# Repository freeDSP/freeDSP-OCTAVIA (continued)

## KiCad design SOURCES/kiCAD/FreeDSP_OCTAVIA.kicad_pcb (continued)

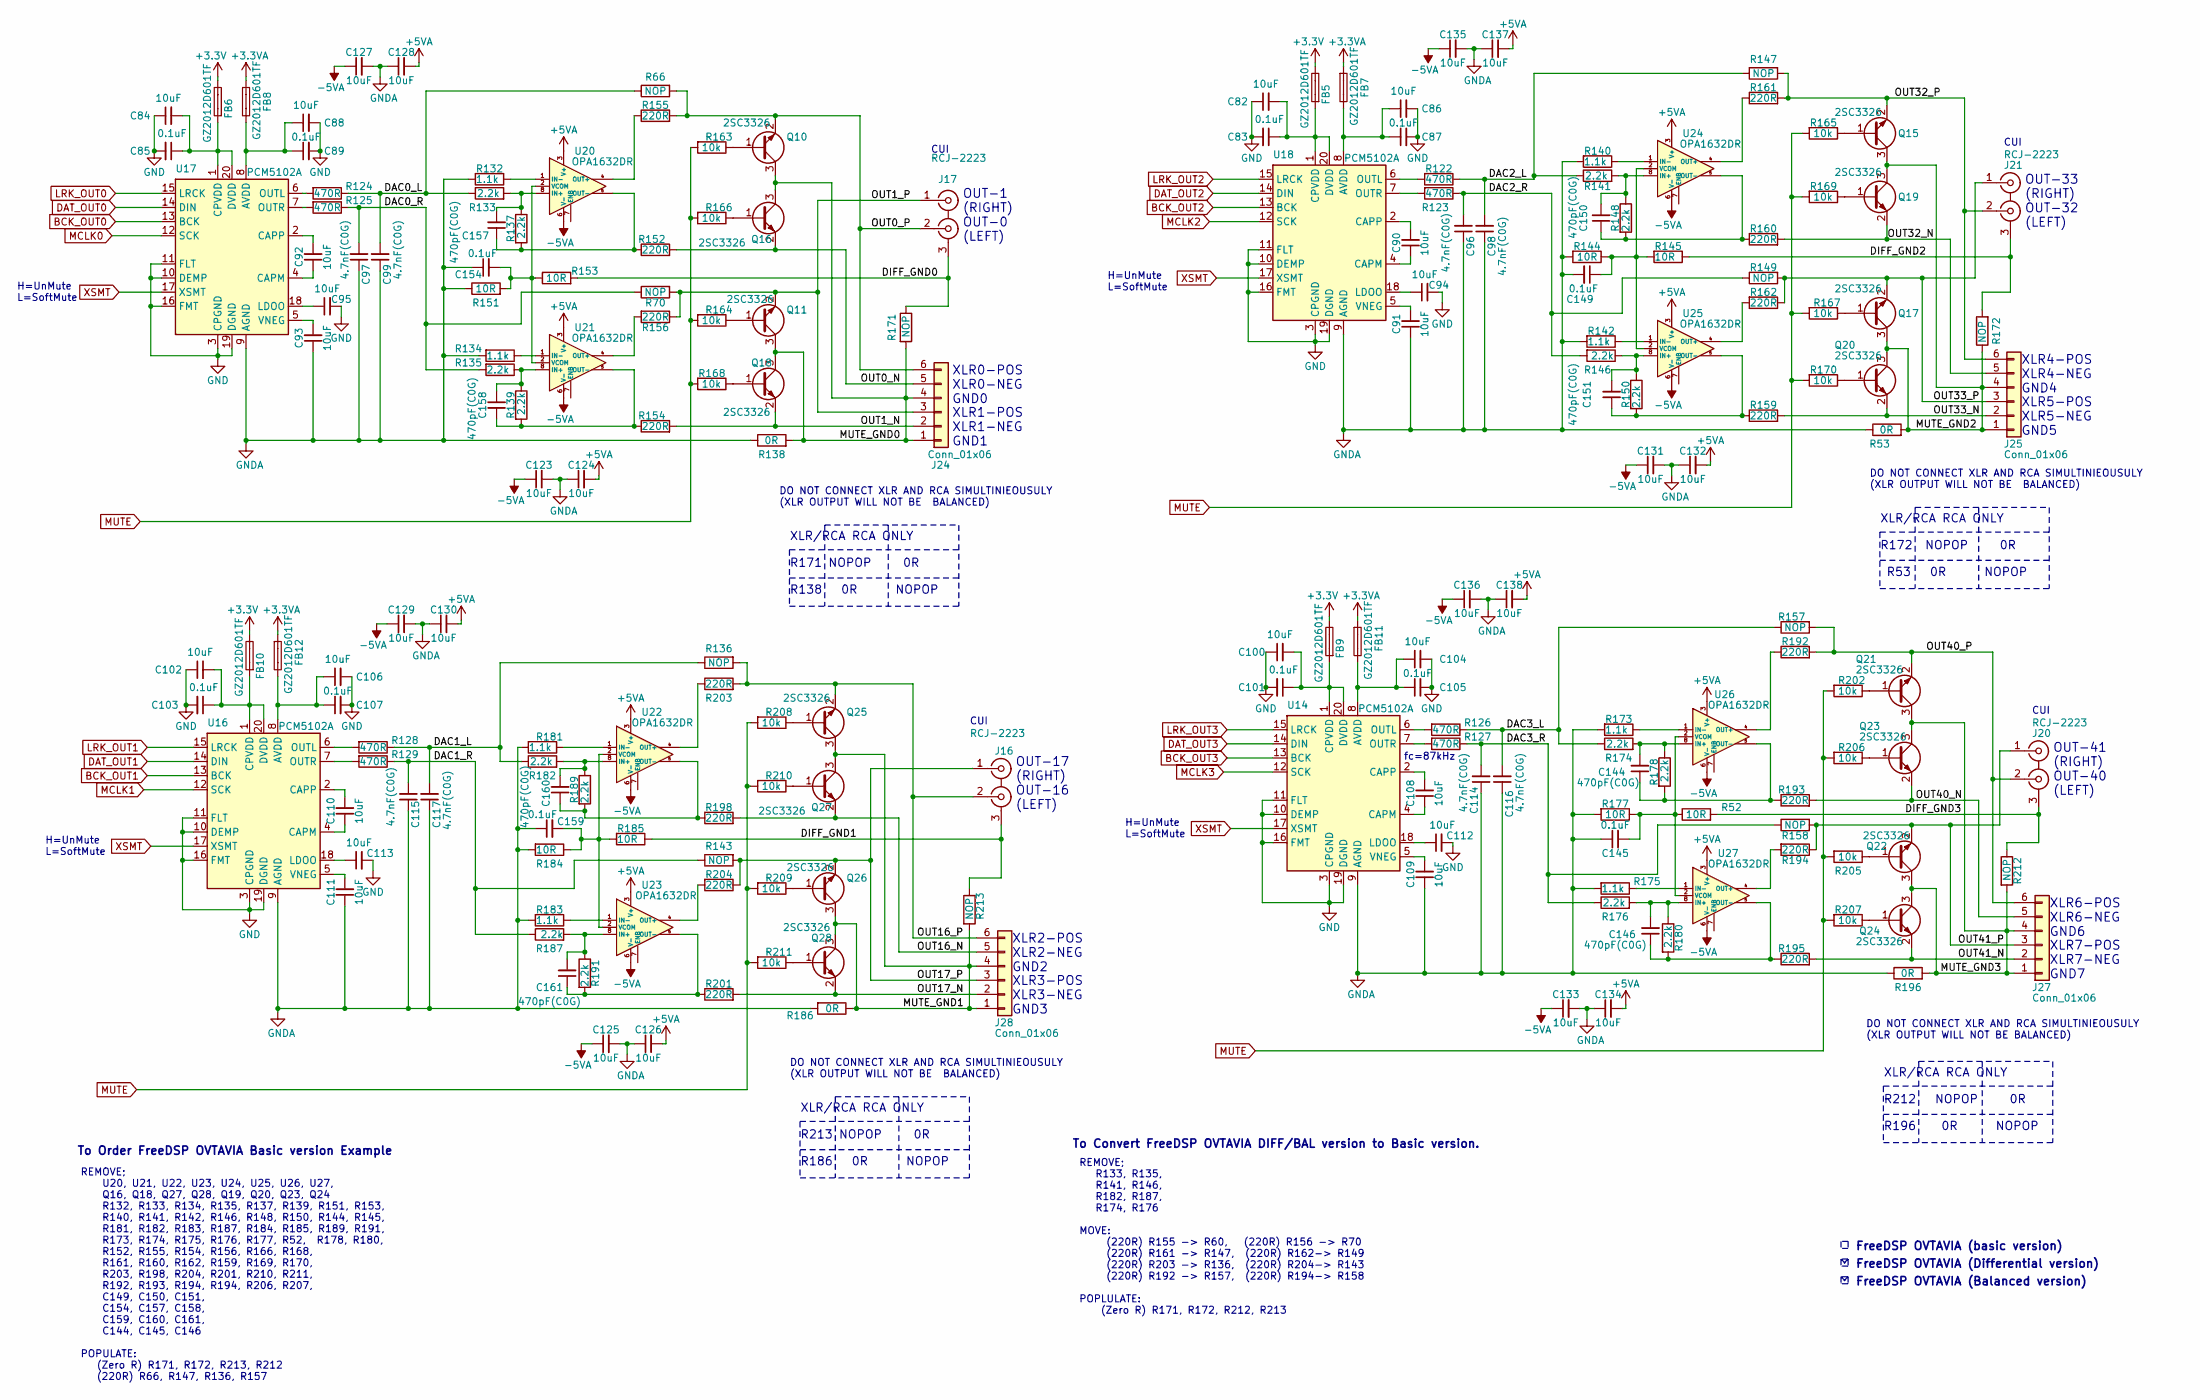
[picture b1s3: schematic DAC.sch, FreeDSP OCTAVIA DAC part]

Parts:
C82, C84, C86, C88, C102, C104, C106: 10uF; C_0805_2012Metric_Pad1.18x1.45mm_HandSolder
C83, C85, C87, C89, C103, C105, C107: 0.1uF; C_0805_2012Metric_Pad1.18x1.45mm_HandSolder
C90, C91, C92, C93, C94, C95, C108, C109, C110, C111, C112, C113, C123, C124, C125, C126, C127, C128, C129, C130, C131, C132, C133, C134, C135, C136, C137, C138: 10uF; C_0603_1608Metric
C96, C97, C98, C99, C114, C115, C116, C117: 4.7nF(C0G); C_0805_2012Metric_Pad1.18x1.45mm_HandSolder
C100: 10uF; C_0805_2012Metric
C101: 0.1uF; C_0805_2012Metric
C144, C146, C150, C151, C157, C158, C160, C161: 470pF(C0G); C_0805_2012Metric_Pad1.18x1.45mm_HandSolder
C145, C149, C154, C159: 0.1uF; C_0603_1608Metric
FB5, FB6, FB7, FB8, FB9, FB10, FB11, FB12: GZ2012D601TF; L_0805_2012Metric_Pad1.15x1.40mm_HandSolder
J16, J17, J20, J21: RCJ-2223
J24, J25, J27, J28: Conn_01x06; PinHeader_1x06_P2.54mm_Vertical
Q10, Q11, Q15, Q16, Q17, Q18, Q19, Q20, Q21, Q22, Q23, Q24, Q25, Q26, Q27, Q28: 2SC3326; SOT-23
R52, R144, R145, R151, R153, R177, R184, R185: 10R; R_0603_1608Metric
R53, R138, R186, R196: 0R; R_0603_1608Metric
R66, R70, R136, R143, R147, R149, R157, R158: NOP; R_0603_HandSoldering
R122, R123, R124, R125, R126, R127, R128, R129: 470R; R_0603_1608Metric
R132, R134, R140, R142, R173, R175, R181, R183: 1.1k; R_0603_1608Metric
R133, R135, R137, R139, R141, R146, R148, R150, R174, R176, R178, R180, R182, R187, R189, R191: 2.2k; R_0603_1608Metric
R152, R154, R155, R156, R159, R160, R161, R162, R192, R193, R194, R195, R198, R201, R203, R204: 220R; R_0603_1608Metric
R163, R164, R165, R166, R167, R168, R169, R170, R202, R205, R206, R207, R208, R209, R210, R211: 10k; R_0603_1608Metric
R171, R172, R212, R213: NOP; R_0603_1608Metric_Pad0.98x0.95mm_HandSolder
U14, U16, U17, U18: PCM5102A; TSSOP-20_4.4x6.5mm_P0.65mm
U20, U21, U22, U23, U24, U25, U26, U27: OPA1632DR; SOIC127P600X175-8N

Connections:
+3.3VA: FB7.1, FB8.1, FB11.1, FB12.1; also elsewhere on the board
+3V3: FB5.2, FB6.2, FB9.2, FB10.2; also elsewhere on the board
+5VA: C124.2, C126.2, C128.2, C130.2, C132.2, C134.2, C137.2, C138.2, U20.3 (V+), U21.3 (V+), U22.3 (V+), U23.3 (V+), U24.3 (V+), U25.3 (V+), U26.3 (V+), U27.3 (V+); also elsewhere on the board
-5VA: C123.1, C125.1, C127.1, C129.1, C131.1, C133.1, C135.1, C136.1, U20.6 (V-), U21.6 (V-), U22.6 (V-), U23.6 (V-), U24.6 (V-), U25.6 (V-), U26.6 (V-), U27.6 (V-); also elsewhere on the board
/ADC_IO Part/DAC/DAC0_L: C99.2, R66.1, R124.1, R133.1
/ADC_IO Part/DAC/DAC0_R: C97.2, R70.1, R125.1, R135.2
/ADC_IO Part/DAC/DAC1_L: C117.2, R128.1, R136.1, R182.1
/ADC_IO Part/DAC/DAC1_R: C115.2, R129.1, R143.1, R187.1
/ADC_IO Part/DAC/DAC2_L: C98.2, R122.1, R141.1, R147.1
/ADC_IO Part/DAC/DAC2_R: C96.2, R123.1, R146.2, R149.1
/ADC_IO Part/DAC/DAC3_L: C116.2, R126.1, R157.1, R174.1
/ADC_IO Part/DAC/DAC3_R: C114.2, R127.1, R158.1, R176.1
/ADC_IO Part/DAC/DIFF_GND0: J17.3 (EXT), R153.2, R171.1
/ADC_IO Part/DAC/DIFF_GND1: J16.3 (EXT), R185.1, R213.1
/ADC_IO Part/DAC/DIFF_GND2: J21.3 (EXT), R145.1, R172.2
/ADC_IO Part/DAC/DIFF_GND3: J20.3 (EXT), R52.2, R212.1
/ADC_IO Part/DAC/MUTE_GND0: J24.1, J24.4, Q10.3 (C), Q11.3 (C), Q16.3 (C), Q18.3 (C), R138.2, R171.2
/ADC_IO Part/DAC/MUTE_GND1: J28.1, J28.4, Q25.3 (C), Q26.3 (C), Q27.3 (C), Q28.3 (C), R186.1, R213.2
/ADC_IO Part/DAC/MUTE_GND2: J25.1, J25.4, Q15.3 (C), Q17.3 (C), Q19.3 (C), Q20.3 (C), R53.2, R172.1
/ADC_IO Part/DAC/MUTE_GND3: J27.1, J27.4, Q21.3 (C), Q22.3 (C), Q23.3 (C), Q24.3 (C), R196.2, R212.2
/ADC_IO Part/DAC/OUT0_N: J24.5, Q16.2 (E), R152.2
/ADC_IO Part/DAC/OUT0_P: J17.2 (IN2), J24.6, Q10.2 (E), R66.2, R155.2
/ADC_IO Part/DAC/OUT1_N: J24.2, Q18.2 (E), R154.2
/ADC_IO Part/DAC/OUT1_P: J17.1 (IN1), J24.3, Q11.2 (E), R70.2, R156.1
/ADC_IO Part/DAC/OUT16_N: J28.5, Q27.2 (E), R198.2
/ADC_IO Part/DAC/OUT16_P: J16.2 (IN2), J28.6, Q25.2 (E), R136.2, R203.2
/ADC_IO Part/DAC/OUT17_N: J28.2, Q28.2 (E), R201.2
/ADC_IO Part/DAC/OUT17_P: J16.1 (IN1), J28.3, Q26.2 (E), R143.2, R204.1
/ADC_IO Part/DAC/OUT32_N: J25.5, Q19.2 (E), R160.2
/ADC_IO Part/DAC/OUT32_P: J21.2 (IN2), J25.6, Q15.2 (E), R147.2, R161.2
/ADC_IO Part/DAC/OUT33_N: J25.2, Q20.2 (E), R159.2
/ADC_IO Part/DAC/OUT33_P: J21.1 (IN1), J25.3, Q17.2 (E), R149.2, R162.1
/ADC_IO Part/DAC/OUT40_N: J27.5, Q23.2 (E), R193.2
/ADC_IO Part/DAC/OUT40_P: J20.2 (IN2), J27.6, Q21.2 (E), R157.2, R192.2
/ADC_IO Part/DAC/OUT41_N: J27.2, Q24.2 (E), R195.2
/ADC_IO Part/DAC/OUT41_P: J20.1 (IN1), J27.3, Q22.2 (E), R158.2, R194.1
BCK_OUT0: U17.13 (BCK); also elsewhere on the board
BCK_OUT1: U16.13 (BCK); also elsewhere on the board
BCK_OUT2: U18.13 (BCK); also elsewhere on the board
BCK_OUT3: U14.13 (BCK); also elsewhere on the board
DAT_OUT0: U17.14 (DIN); also elsewhere on the board
DAT_OUT1: U16.14 (DIN); also elsewhere on the board
DAT_OUT2: U18.14 (DIN); also elsewhere on the board
DAT_OUT3: U14.14 (DIN); also elsewhere on the board
GND: C82.1, C83.2, C84.1, C85.2, C86.2, C87.2, C88.2, C89.2, C94.2, C95.2, C100.1, C101.2, C102.1, C103.2, C104.2, C105.2, C106.2, C107.2, C112.2, C113.2, U14.3 (CPGND), U14.10 (DEMP), U14.11 (FLT), U14.16 (FMT), U14.19 (DGND), U16.3 (CPGND), U16.10 (DEMP), U16.11 (FLT), U16.16 (FMT), U16.19 (DGND), U17.3 (CPGND), U17.10 (DEMP), U17.11 (FLT), U17.16 (FMT), U17.19 (DGND), U18.3 (CPGND), U18.10 (DEMP), U18.11 (FLT), U18.16 (FMT), U18.19 (DGND); also elsewhere on the board
GNDA: C91.1, C93.1, C96.1, C97.1, C98.1, C99.1, C109.1, C111.1, C114.1, C115.1, C116.1, C117.1, C123.2, C124.1, C125.2, C126.1, C127.2, C128.1, C129.2, C130.1, C131.2, C132.1, C133.2, C134.1, C135.2, C136.2, C137.1, C138.1, C145.1, C149.2, C154.1, C159.1, R53.1, R132.2, R134.2, R138.1, R140.2, R142.2, R144.2, R151.1, R173.2, R175.2, R177.2, R181.2, R183.2, R184.2, R186.2, R196.1, U14.9 (AGND), U16.9 (AGND), U17.9 (AGND), U18.9 (AGND); also elsewhere on the board
LRK_OUT0: U17.15 (LRCK); also elsewhere on the board
LRK_OUT1: U16.15 (LRCK); also elsewhere on the board
LRK_OUT2: U18.15 (LRCK); also elsewhere on the board
LRK_OUT3: U14.15 (LRCK); also elsewhere on the board
MCLK0: U17.12 (SCK); also elsewhere on the board
MCLK1: U16.12 (SCK); also elsewhere on the board
MCLK2: U18.12 (SCK); also elsewhere on the board
MCLK3: U14.12 (SCK); also elsewhere on the board
MUTE: R163.2, R164.2, R165.2, R166.2, R167.2, R168.2, R169.2, R170.2, R202.2, R205.2, R206.2, R207.2, R208.2, R209.2, R210.2, R211.2; also elsewhere on the board
unnamed: C82.2, C83.1, FB5.1, U18.1 (CPVDD), U18.20 (DVDD)
unnamed: C84.2, C85.1, FB6.1, U17.1 (CPVDD), U17.20 (DVDD)
unnamed: C86.1, C87.1, FB7.2, U18.8 (AVDD)
unnamed: C88.1, C89.1, FB8.2, U17.8 (AVDD)
unnamed: C90.1, U18.4 (CAPM)
unnamed: C90.2, U18.2 (CAPP)
unnamed: C91.2, U18.5 (VNEG)
unnamed: C92.1, U17.4 (CAPM)
unnamed: C92.2, U17.2 (CAPP)
unnamed: C93.2, U17.5 (VNEG)
unnamed: C94.1, U18.18 (LDOO)
unnamed: C95.1, U17.18 (LDOO)
unnamed: C100.2, C101.1, FB9.1, U14.1 (CPVDD), U14.20 (DVDD)
unnamed: C102.2, C103.1, FB10.1, U16.1 (CPVDD), U16.20 (DVDD)
unnamed: C104.1, C105.1, FB11.2, U14.8 (AVDD)
unnamed: C106.1, C107.1, FB12.2, U16.8 (AVDD)
unnamed: C108.1, U14.4 (CAPM)
unnamed: C108.2, U14.2 (CAPP)
unnamed: C109.2, U14.5 (VNEG)
unnamed: C110.1, U16.4 (CAPM)
unnamed: C110.2, U16.2 (CAPP)
unnamed: C111.2, U16.5 (VNEG)
unnamed: C112.1, U14.18 (LDOO)
unnamed: C113.1, U16.18 (LDOO)
unnamed: C144.1, R178.2, R193.1, U26.5 (OUT-)
unnamed: C144.2, R174.2, R178.1, U26.8 (IN+)
unnamed: C145.2, R52.1, R177.1, U26.2 (VCOM), U27.2 (VCOM)
unnamed: C146.1, R180.2, R195.1, U27.5 (OUT-)
unnamed: C146.2, R176.2, R180.1, U27.8 (IN+)
unnamed: C149.1, R144.1, R145.2, U24.2 (VCOM), U25.2 (VCOM)
unnamed: C150.1, R148.2, R160.1, U24.5 (OUT-)
unnamed: C150.2, R141.2, R148.1, U24.8 (IN+)
unnamed: C151.1, R150.2, R159.1, U25.5 (OUT-)
unnamed: C151.2, R146.1, R150.1, U25.8 (IN+)
unnamed: C154.2, R151.2, R153.1, U20.2 (VCOM), U21.2 (VCOM)
unnamed: C157.1, R137.2, R152.1, U20.5 (OUT-)
unnamed: C157.2, R133.2, R137.1, U20.8 (IN+)
unnamed: C158.1, R139.2, R154.1, U21.5 (OUT-)
unnamed: C158.2, R135.1, R139.1, U21.8 (IN+)
unnamed: C159.2, R184.1, R185.2, U22.2 (VCOM), U23.2 (VCOM)
unnamed: C160.1, R189.2, R198.1, U22.5 (OUT-)
unnamed: C160.2, R182.2, R189.1, U22.8 (IN+)
unnamed: C161.1, R191.2, R201.1, U23.5 (OUT-)
unnamed: C161.2, R187.2, R191.1, U23.8 (IN+)
unnamed: Q10.1 (B), R163.1
unnamed: Q11.1 (B), R164.1
unnamed: Q15.1 (B), R165.1
unnamed: Q16.1 (B), R166.1
unnamed: Q17.1 (B), R167.1
unnamed: Q18.1 (B), R168.1
unnamed: Q19.1 (B), R169.1
unnamed: Q20.1 (B), R170.1
unnamed: Q21.1 (B), R202.1
unnamed: Q22.1 (B), R205.1
unnamed: Q23.1 (B), R206.1
unnamed: Q24.1 (B), R207.1
unnamed: Q25.1 (B), R208.1
unnamed: Q26.1 (B), R209.1
unnamed: Q27.1 (B), R210.1
unnamed: Q28.1 (B), R211.1
unnamed: R122.2, U18.6 (OUTL)
unnamed: R123.2, U18.7 (OUTR)
unnamed: R124.2, U17.6 (OUTL)
unnamed: R125.2, U17.7 (OUTR)
unnamed: R126.2, U14.6 (OUTL)
unnamed: R127.2, U14.7 (OUTR)
unnamed: R128.2, U16.6 (OUTL)
unnamed: R129.2, U16.7 (OUTR)
unnamed: R132.1, U20.1 (IN-)
unnamed: R134.1, U21.1 (IN-)
unnamed: R140.1, U24.1 (IN-)
unnamed: R142.1, U25.1 (IN-)
unnamed: R155.1, U20.4 (OUT+)
unnamed: R156.2, U21.4 (OUT+)
unnamed: R161.1, U24.4 (OUT+)
unnamed: R162.2, U25.4 (OUT+)
unnamed: R173.1, U26.1 (IN-)
unnamed: R175.1, U27.1 (IN-)
unnamed: R181.1, U22.1 (IN-)
unnamed: R183.1, U23.1 (IN-)
unnamed: R192.1, U26.4 (OUT+)
unnamed: R194.2, U27.4 (OUT+)
unnamed: R203.1, U22.4 (OUT+)
unnamed: R204.2, U23.4 (OUT+)
XSMT: U14.17 (XSMT), U16.17 (XSMT), U17.17 (XSMT), U18.17 (XSMT); also elsewhere on the board

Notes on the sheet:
FreeDSP OVTAVIA (basic version)
FreeDSP OVTAVIA (Differential version)
XLR6-POS XLR6-NEG GND6
XLR2-POS XLR2-NEG GND2
XLR5-POS XLR5-NEG GND5
XLR7-POS XLR7-NEG GND7
XLR3-POS XLR3-NEG GND3
XLR1-POS XLR1-NEG GND1
XLR4-POS XLR4-NEG GND4
XLR0-POS XLR0-NEG GND0
OUT-33 (RIGHT) OUT-32 (LEFT)
OUT-41 (RIGHT) OUT-40 (LEFT)
OUT-17 (RIGHT) OUT-16 (LEFT)
To Order FreeDSP OVTAVIA Basic version Example
XLR/RCA RCA ONLY R212 NOPOP 0R R196 0R NOPOP
REMOVE; U20, U21, U22, U23, U24, U25, U26, U27, Q16, Q18, Q27, Q28, Q19, Q20, Q23, Q24 R132, R133, R134, R135, R137, R139, R151, R153, R140, R141, R142, R146, R148, R150, R144, R145, R181, R182, R183, R187, R184, R185, R189, R191, R173, R174, R175, R176, R177, R52, R178, R180, R152, R155, R154, R15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
H=UnMute L=SoftMute
FreeDSP OVTAVIA (Balanced version)
DO NOT CONNECT XLR AND RCA SIMULTINIEOUSULY (XLR OUTPUT WILL NOT BE BALANCED)
DO NOT CONNECT XLR AND RCA SIMULTINIEOUSULY (XLR OUTPUT WILL NOT BE BALANCED)
OUT-1 (RIGHT) OUT-0 (LEFT)
XLR/RCA RCA ONLY R171 NOPOP 0R R138 0R NOPOP
XLR/RCA RCA ONLY R213 NOPOP 0R R186 0R NOPOP
XLR/RCA RCA ONLY R172 NOPOP 0R R53 0R NOPOP
fc=87kHz
CUI
To Convert FreeDSP OVTAVIA DIFF/BAL version to Basic version.
REMOVE; R133, R135, R141, R146, R182, R187, R174, R176 MOVE: (220R) R155 -> R60, (220R) R156 -> R70 (220R) R161 -> R147, (220R) R162-> R149 (220R) R203 -> R136, (220R) R204-> R143 (220R) R192 -> R157, (220R) R194-> R158 POPLULATE: (Zero R) R171, R172, R212, R213

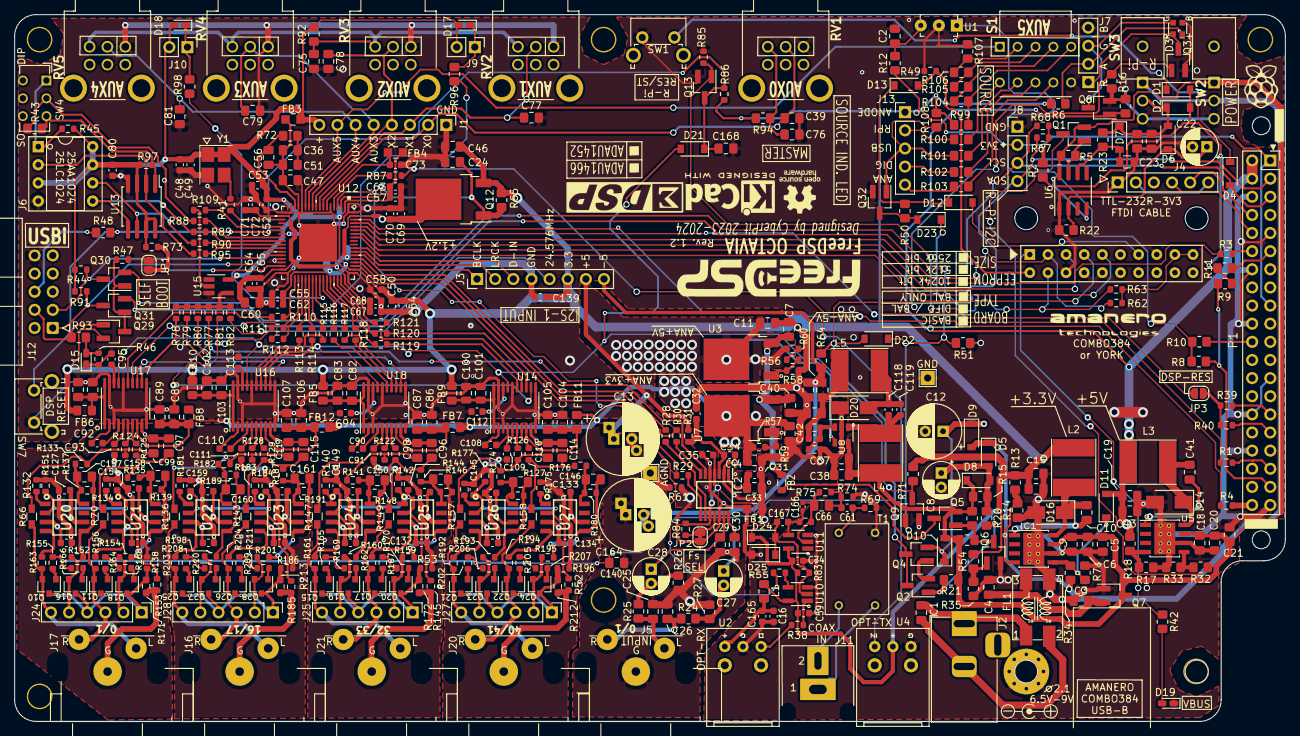
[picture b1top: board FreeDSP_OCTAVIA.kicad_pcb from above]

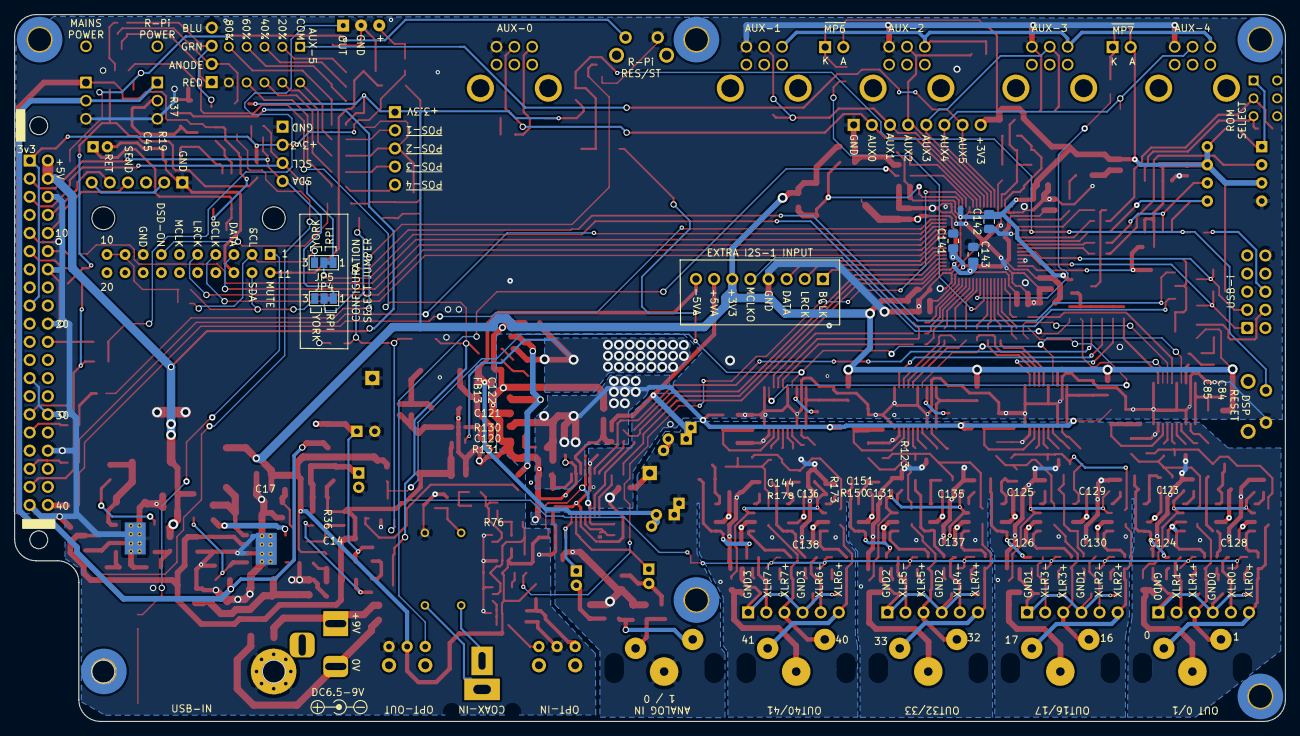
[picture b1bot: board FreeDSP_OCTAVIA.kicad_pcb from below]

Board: 4 copper layers, 178.0 x 99.0 mm, 525 parts (15 on the bottom side), 314 nets.

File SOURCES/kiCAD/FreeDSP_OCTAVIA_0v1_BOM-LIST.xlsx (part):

FreeDSP OCTAVIA Differential/Balanced Output Version BOM List
Date: | Wednesday, 15 March 2023 at 00:45:07
Component Count: | 487
Item | JLPCB# | Qty | Reference(s) | Value | Footprint | Description | Digi-Key_PN | Shop URL
 | HAND |  | A1 | Combo384 | MyLibrary:Combo384 | Amanero Combo384 or Compatible Module 20P Socket
 | OPTION |  | J6 | 8P_DIP_SOCKET | Package_DIP:DIP-8_W7.62mm_Socket | Only Mount if you need to use DIP package EEPROM
 | NOP |  | C66 | NOP | Capacitor_SMD:C_0805_2012Metric_Pad1.18x1.45mm_HandSolder
 | NOP |  | R9 | NOP | Resistor_SMD:R_0805_2012Metric_Pad1.20x1.40mm_HandSolder
 | NOP |  | R10 | NOP | Resistor_SMD:R_0805_2012Metric_Pad1.20x1.40mm_HandSolder
 | NOP |  | R40 | NOP | Resistor_SMD:R_0603_1608Metric
 | NOP |  | R143 | NOP | Resistor_SMD:R_0603_1608Metric
 | NOP |  | R144 | NOP | Resistor_SMD:R_0603_1608Metric
 | NOP |  | R145 | NOP | Resistor_SMD:R_0603_1608Metric
 | NOP |  | R184 | NOP | Resistor_SMD:R_0603_1608Metric
 | NOP |  | R185 | NOP | Resistor_SMD:R_0603_1608Metric
 | NOP |  | R186 | NOP | Resistor_SMD:R_0603_1608Metric
 | HAND |  | J1 | Conn_01x08 | Connector_PinHeader_2.54mm:PinHeader_1x08_P2.54mm_Vertical
 | HAND |  | J3 | Conn_01x08 | Connector_PinHeader_2.54mm:PinHeader_1x08_P2.54mm_Vertical
 | HAND |  | J4 | Header_01x06 | Connector_PinHeader_2.54mm:PinHeader_1x06_P2.54mm_Vertical
 | HAND |  | J5 | Conn_Coaxial_x2 | MyCompo:MJ-519 |  |  | https://akizukidenshi.com/catalog/g/gC-12480/
 | HAND |  | J8 | Header_01x04 | Connector_PinHeader_2.54mm:PinHeader_1x04_P2.54mm_Vertical
 | HAND |  | J11 | Conn_Coaxial | MyJacks:RJ-2410N | Yellow for SPDIF Coax. |  | https://akizukidenshi.com/catalog/g/gC-06508/
 | HAND |  | J12 | IDC_2x5 | Connector_IDC:IDC-Header_2x05_P2.54mm_Horizontal | or Angle type, for USBi
 | HAND |  | J13 | Conn_01x05 | Connector_PinHeader_2.54mm:PinHeader_1x05_P2.54mm_Vertical
 | HAND |  | J16 | MJ-519 | MyJacks:MJ-519 |  |  | https://akizukidenshi.com/catalog/g/gC-12480/
 | HAND |  | J17 | MJ-519 | MyJacks:MJ-519 |  |  | https://akizukidenshi.com/catalog/g/gC-12480/
 | HAND |  | J20 | MJ-519 | MyJacks:MJ-519 |  |  | https://akizukidenshi.com/catalog/g/gC-12480/
 | HAND |  | J21 | MJ-519 | MyJacks:MJ-519 |  |  | https://akizukidenshi.com/catalog/g/gC-12480/
 | HAND |  | J24 | Header6P | Connector_PinHeader_2.54mm:PinHeader_1x06_P2.54mm_Vertical
 | HAND |  | J25 | Conn_01x06 | Connector_PinHeader_2.54mm:PinHeader_1x06_P2.54mm_Vertical
 | HAND |  | J27 | Conn_01x06 | Connector_PinHeader_2.54mm:PinHeader_1x06_P2.54mm_Vertical
 | HAND |  | J28 | Header6P | Connector_PinHeader_2.54mm:PinHeader_1x06_P2.54mm_Vertical
 | HAND |  | P1 | Conn_02x20_Odd_Even | Connector_PinSocket_2.54mm:PinSocket_2x20_P2.54mm_Vertical
 | HAND |  | SW4 | SW_NOP_DPDT | Buttons_Switches_ThroughHole:SW_CuK_JS202011AQN_DPDT_Angled
 | HAND |  | C8 | 22uF/16V | Capacitor_THT:CP_Radial_D5.0mm_P2.00mm
 | HAND |  | C12 | 220uF/16V | Capacitor_THT:CP_Radial_D7.5mm_P2.50mm
 | HAND |  | C13 | 220uF/6.3V | Capacitor_THT:CP_Radial_D5.0mm_P2.00mm
 | HAND |  | C22 | 33uF/16V | Capacitor_THT:CP_Radial_D5.0mm_P2.00mm
 | HAND |  | C27 | 2.2uF | Capacitor_THT:CP_Radial_D5.0mm_P2.00mm
 | HAND |  | C28 | 2.2uF | Capacitor_THT:CP_Radial_D5.0mm_P2.00mm
 | HAND |  | J2 | DC12V-IN | Connector_BarrelJack:BarrelJack_Horizontal
 | HAND |  | RV1 | B10K | Myfootprints:RK09L12B0A31
 | HAND |  | RV2 | B10K | Myfootprints:RK09L12B0A31
 | HAND |  | RV3 | B10K | Myfootprints:RK09L12B0A31
 | HAND |  | RV4 | B10K | Myfootprints:RK09L12B0A31
 | HAND |  | RV5 | B10K | Myfootprints:RK09L12B0A31
 | HAND |  | S1 | SR10010F-0204-20F0B-C7-N-0027_ALT | Myfootprints:SR10010F020420F0BC7N0027 | Rotary Switches 2 POLE 4 POS D SHAFT |  | https://akizukidenshi.com/catalog/g/gP-16034/
 | HAND |  | SW1 | SW_Push | OPL_Switch:SW2-5.0-6.0X3.0X4.3MM
 | HAND |  | SW2 | SW_SPDT | Myfootprints:2MS1T1B4M7QES
 | HAND |  | SW3 | SW_SPDT | Myfootprints:2MS1T1B4M7QES
 | HAND |  | SW7 | DSP_RES | OPL_Switch:SW2-5.0-6.0X3.0X4.3MM | SWITCH PUSHBUTTON SPST 1A 30V | CW181-ND
 | HAND |  | T1 | PE-65612NL | PE65612NL | Audio Transformers / Signal Transformers THT Digital Audio 2500uH 1-Port
 | HAND |  | U1 | GP1UXC41QS | digikey-footprints:IR_Receiver_TSOP38238 | SENSOR REMOTE REC 38.0KHZ 45M | 751-1227-ND
 | HAND |  | U2 | PLR135-T10 | MyLibrary:PLR135-T10
 | HAND |  | U4 | PLT133-T10W | MyLibrary:PLT133-T10W
 | C9864 |  | IC1 | TPS5430DDA | Package_SO:TI_SO-PowerPAD-8_ThermalVias
 | C9864 |  | U5 | TPS5430DDA | Package_SO:TI_SO-PowerPAD-8_ThermalVias
 | C965848 |  | D3 | LED_ABGR | MyLED:LED_0603_ABGR
 | C96446 |  | C34 | 10uF | Capacitor_SMD:C_0603_1608Metric
 | C96446 |  | C50 | 10uF | Capacitor_SMD:C_0603_1608Metric
 | C96446 |  | C90 | 10uF | Capacitor_SMD:C_0603_1608Metric
 | C96446 |  | C91 | 10uF | Capacitor_SMD:C_0603_1608Metric
 | C96446 |  | C92 | 10uF | Capacitor_SMD:C_0603_1608Metric
 | C96446 |  | C93 | 10uF | Capacitor_SMD:C_0603_1608Metric
 | C96446 |  | C94 | 10uF | Capacitor_SMD:C_0603_1608Metric
 | C96446 |  | C95 | 10uF | Capacitor_SMD:C_0603_1608Metric
 | C96446 |  | C108 | 10uF | Capacitor_SMD:C_0603_1608Metric
 | C96446 |  | C109 | 10uF | Capacitor_SMD:C_0603_1608Metric
 | C96446 |  | C110 | 10uF | Capacitor_SMD:C_0603_1608Metric
 | C96446 |  | C111 | 10uF | Capacitor_SMD:C_0603_1608Metric
 | C96446 |  | C112 | 10uF | Capacitor_SMD:C_0603_1608Metric
 | C96446 |  | C113 | 10uF | Capacitor_SMD:C_0603_1608Metric
 | C96446 |  | C123 | 10uF | Capacitor_SMD:C_0603_1608Metric
 | C96446 |  | C124 | 10uF | Capacitor_SMD:C_0603_1608Metric
 | C96446 |  | C125 | 10uF | Capacitor_SMD:C_0603_1608Metric
 | C96446 |  | C126 | 10uF | Capacitor_SMD:C_0603_1608Metric
 | C96446 |  | C127 | 10uF | Capacitor_SMD:C_0603_1608Metric
 | C96446 |  | C128 | 10uF | Capacitor_SMD:C_0603_1608Metric
 | C96446 |  | C129 | 10uF | Capacitor_SMD:C_0603_1608Metric
 | C96446 |  | C130 | 10uF | Capacitor_SMD:C_0603_1608Metric
 | C96446 |  | C131 | 10uF | Capacitor_SMD:C_0603_1608Metric
 | C96446 |  | C132 | 10uF | Capacitor_SMD:C_0603_1608Metric
 | C96446 |  | C133 | 10uF | Capacitor_SMD:C_0603_1608Metric
 | C96446 |  | C134 | 10uF | Capacitor_SMD:C_0603_1608Metric
 | C96446 |  | C135 | 10uF | Capacitor_SMD:C_0603_1608Metric
 | C96446 |  | C136 | 10uF | Capacitor_SMD:C_0603_1608Metric
 | C96446 |  | C137 | 10uF | Capacitor_SMD:C_0603_1608Metric
 | C96446 |  | C138 | 10uF | Capacitor_SMD:C_0603_1608Metric
 | C908578 |  | FL1 | ACM9070 | MyLibrary:ACM9070 | TDK - ACM9070-701-2PL-TL01 - FILTER, COMMON MODE, 5A, SMD
 | C90760 |  | U6 | LMC555CMX | Package_SO:SOIC-8_3.9x4.9mm_P1.27mm
 | C86715 |  | U20 | OPA1632DR | Myfootprints:SOIC127P600X175-8N
 | C86715 |  | U21 | OPA1632DR | Myfootprints:SOIC127P600X175-8N
 | C86715 |  | U22 | OPA1632DR | Myfootprints:SOIC127P600X175-8N
 | C86715 |  | U23 | OPA1632DR | Myfootprints:SOIC127P600X175-8N
 | C86715 |  | U24 | OPA1632DR | Myfootprints:SOIC127P600X175-8N
 | C86715 |  | U25 | OPA1632DR | Myfootprints:SOIC127P600X175-8N
 | C86715 |  | U26 | OPA1632DR | Myfootprints:SOIC127P600X175-8N
 | C86715 |  | U27 | OPA1632DR | Myfootprints:SOIC127P600X175-8N
 | C8598 |  | D9 | SS2040FL | Diode_SMD:D_SOD-123
 | C8598 |  | D10 | SS2040FL | Diode_SMD:D_SOD-123
 | C8545 |  | Q3 | 2N7002 | Package_TO_SOT_SMD:SOT-23_Handsoldering
 | C8545 |  | Q6 | 2N7002 | Package_TO_SOT_SMD:SOT-23_Handsoldering
 | C8545 |  | Q8 | 2N7002 | Package_TO_SOT_SMD:SOT-23_Handsoldering
 | C8545 |  | Q9 | 2N7002 | Package_TO_SOT_SMD:SOT-23_Handsoldering
 | C8545 |  | Q13 | 2N7002 | Package_TO_SOT_SMD:SOT-23_Handsoldering
 | C8545 |  | Q14 | 2N7002 | Package_TO_SOT_SMD:SOT-23_Handsoldering
 | C8545 |  | Q30 | 2N7002 | Package_TO_SOT_SMD:SOT-23_Handsoldering
 | C8545 |  | Q31 | 2N7002 | Package_TO_SOT_SMD:SOT-23_Handsoldering
 | C8326 |  | Q2 | MMBT5401 | Package_TO_SOT_SMD:SOT-23_Handsoldering
 | C8326 |  | Q4 | MMBT5401 | Package_TO_SOT_SMD:SOT-23_Handsoldering
 | C81598 |  | D1 | 1N4148W | Diode_SMD:D_SOD-123
 | C81598 |  | D2 | 1N4148W | Diode_SMD:D_SOD-123
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
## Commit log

2023-03-14 Initial Prototype Version0.1
2023-03-14 Rendering Images
2023-03-14 Caution: Not Build/verified yet.
2023-03-19 Figure Images
2023-04-07 Updated version0.2
2023-04-15 Updated description about SPI EEPROM.
2023-04-15 version 0.2 updates
2023-04-18 Add files via upload
    Raspberry-Pi Power Control Demo
2023-04-19 Fixed missing SMD Beads
2023-04-19 Actual Board Picture
2023-04-22 Count on J5 in hand-mount BOM list.
2023-04-24 Workaround photos
    Offset mounted C13、Removed D13, Reversed D21
2023-04-26 ADC,USB,RPI works SPDIF is not yet,
2023-04-28 Change R76 to fix the coax input
2023-04-28 Programming setting for M95256
2023-04-28 RPI, USB, S/PDIF, RCA Input ready
2023-04-28 Lookup-Table for source selector
2023-04-29 3way Crossover Example Schematic
2023-04-29 3way Crossover Divider Example project
2023-04-29 Now Working photo
2023-04-30 Block Diagrams
2023-04-30 Block Diagram
2023-04-30 SPDIF I/F Schematic
2023-04-30 SPDIF I/F part schematic
2023-05-01 D13 placement, R76 value changed, D21 removed
2023-05-06 Design the Original Chassis
2023-05-07 Installed Photo
2023-05-07 R7 R33 Value Changed
2023-05-07 R33, R7 Changed
2023-05-08 Updated to Wide Supply Voltage Version
2023-05-13 Issue Fixed, Header Added, Heatspreader Added
2023-05-13 Version0.2 Board. Reviced PCB design.
2023-05-13 Updated PCB design. Issue fixed.
2023-05-14 Add some comment strings
2023-05-14 Physical Board Information
2023-05-14 Adjusted to actual sizes
2023-05-14 Updated version 0.2 image renderings
2023-05-14 3way C/D with Delay and Gain Trim.
2023-05-14 3way C/D with Delay & Gain Trim (MF, HF only)
2023-05-14 Default SigmaStudio Project Start Template
2023-05-14 Defalut SigmaStudio Startpoint Project (96kHz)
2023-05-14 Update README.md
    Design Released
2023-05-15 Error Fixed, Add Lo-End Compensaton EQ
2023-05-17 More sample project uploaaaded
2023-05-20 Power Status Indicator LED moved
2023-05-20 ASRC issue fixed
2023-05-20 Fixed ASRC Issue
2023-05-22 ver2.0 mute function updated
2023-05-24 Fixed wrong L/R Connection of RCA Jack
2023-05-25 Master Volume Curve Updated
2023-06-06 Clock setting fixed
2023-07-22 Second Trial Version
2023-07-22 Enhanced Release Version (4 Layer PCB Design)
2023-07-22 2nd Trial Version (2 Layer PCB)
2023-07-22 The last 2 Layer PCB Design version
2023-07-22 New Output Driver with Enhanced 4 Layer PCB
2023-07-22 New Output Driver with 4 Layer PCB ver0.30 Archive
2023-07-22 New Output Driver with 4 Layer PCB
2023-07-25 Fixed USB position of Source Selector SW
    Version 3.0 design was CCW position equals USB. (USB-RPi-DIG-ANA)
    Version 3.1 is swapped with RPi (RPI-USB-DIG-ANA)
2023-07-25 Fixed USB Position of Source Selector Switch
    Version 0.30 (CCW) USB - RPi - DIG -ANA (CW)
    Version 0.31 (CCW) RPi - USB - DIG -ANA (CW)
2023-07-25 Source Select SW (USB - RPi - DIG - ANA)
2023-07-25 Fixed USB Position of Source Selector Switch
    Fixed USB Position of Source Selector Switch
    Version 0.30 (CCW) USB - RPi - DIG -ANA (CW)
    Version 0.31 (CCW) RPi - USB - DIG -ANA (CW)
2023-07-25 FIxed USB position of Source Selector
    Fixed USB Position of Source Selector Switch
    Version 0.30 (CCW) USB - RPi - DIG -ANA (CW)
    Version 0.31 (CCW) RPi - USB - DIG -ANA (CW)
2023-08-15 Improved Coax Input Noise Immunities
2023-08-15 Improved Coax Input Noise Immunities
    Changed Coax input amp design and AC couling to EXOR
2023-08-15 Update ver 0.32 README.md
    The coaxial S/PDIF input circuit is updated, with no other changes.
2023-08-15 ver0.32 Improved Coaxial Input Noise Immunity.
2023-08-28 Voltage Regurator had Changed to LM317
2023-08-28 Voltage Regulator Changed to LM317
    PCB layout is also updated in some of the places.
2023-08-28 Version 0.33 Updated
    Only the change of Voltage Regulator.
2023-09-06 Rendering Image with RPI
2023-09-28 Just evaluation use only. (Do not build)
2023-09-28 Just evaluation only used in Japan.
2023-09-29 Only used for evaluation in Japan.
2023-09-29 Fixed Evaluation use only.
2023-09-29 Not evaluated but fixed issues in 0v33j
2023-09-30 Released for everyone ready to build.
2023-09-30 Released for everyone, ready to build.
2023-09-30 Create LICENSE
2023-10-07 Fixed R57, R59 value errors
2023-11-05 A Fun Project Play Along with Electric Guitar
    An Electric Guitar Amplifier Simulator with Audio Source Mixer.
2023-11-07 A Fun Project Play Along with Electric Guitar, IRs
2023-11-13 Fixed Clock Domain and LUT setting issues
2023-11-26 Crossover distortion feature added
2023-11-28 Fixed ACM9070F Land Patterns.
2023-12-03 Delete SOURCES/kiCAD/FreeDSP_OCTAVIA_1v02_20231129.zip
    Found short connection issue.
2023-12-03 Delete SOURCES/kiCAD/JLPCB_Oder files (DIFF and BAL)/1v02 directory
    A short connection was found.
    Do not use this version 1.02
2023-12-03 Fixed ACM9070 lands. Selectable I2C for RPI/YORK
2023-12-12 Example 3way C/D Balance/Delay Ctrls with EQ
2023-12-27 Adjust Some Gains on each Blocks
2024-01-02 A method of board type convertion had changed.
    No functions/features changed.
2024-01-02 A method of board type convertion had changed.
    Add an AGND fill on the bottom layer. The connection path for the Standard type board had changed. No features/functions changed.
2024-01-02 A method of board type convertion had changed.
2024-09-21 Fixed AMANERO USB card size and mounting holes.
2024-11-24 Remove C24 to Improve DVDD stability
2025-04-28 Variable Crossover LR8 3way Channel Divider
2025-04-30 Fixed LR8 Filter Curves(Fc50-500Hz, 120-12kHz)
2025-05-01 LR8 Crossover: Fixed AUX-ADC AM noise issue
